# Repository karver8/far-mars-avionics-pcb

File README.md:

# far-mars-avionics-controller

The **far-mars-avionics-controller** is a custom built printed circuit board that performs data aquisition, logging, and communication, all in one highly power effecient, light weight, and compact design. This circuit was built around the FAR/MARS rocket competition, which challenges teams to design a LOX/Methane rocket to accuratley target an altitude of 45,000 feet.

### Features
* Dual(5V/3.3V) Supply ARM Cortex M0+ microcontroller
* 9 multi-purpose 5V I/O pins (+1 DIO PIN)
* Up to 9 12bit and 2 16bit Analog to Digital channels.
* RS-485 Transceiver for long distance LVDS ground communications
* CANbus Transceiver for future feature expansion(untested)
* BNO055 Inertial Measurement Unit
* Locking microSD card slot for secure, vibration resistant data logging
* 5-17V Input Range allowing for versatile power supply.
* Power Effecient enabling the use of a tiny battery
* Very light, weighs less than an ounce!
* Built-in battery charge monitoring.
* Highly accurate crystal for detailed timestamping.

### Firmware

The FAR/MARS rocket uses a FreeRTOS implementation to safley and predictabley manage the various avionics tasks required to launch the rocket. Documentation and development of the firmware for this board can be found in our [far-mars-onboard-firmware](https://github.com/SDSURocketProject/far-mars-onboard-firmware) repository. 

### Documentation
Here is everything you need to interface with this PCB and/or to write your own drivers and firmware:
* [Pinout](/documentation/pinout.pdf "Pinout")
* [Schematic](/documentation/schematic.pdf "Schematic")
* [Mechanical Drawing](/documentation/mech_drawing.pdf "Drawing")
* [Device Datasheet Collection](/documentation/Datasheets "Device Datasheet Collection")

### Assembly
It is highly recommend that you outsource the assembly of this PCB. This design has a lot of tiny surface mount components, on both sides of the board, so unless you have experience reflowing on two sides, this will be almost impossible to assemble yourself. We used MacroFab for the most recent version of this PCB. The current BOM is also optimized to take advantage of their 10-day turnaround service. Here is everything you need to assemble your own avionics controller:
* [Assembly Guide](/assembly#assembly-guide "Instructions")
* [Bill of Materials](/assembly/BOM#bill-of-materials "Bill of Materials")
* [Gerber Files](/assembly/Gerbers)
* [Design Slides](/assembly/Physical%20Summary.pdf "Physical Summary")
* **Schematic & Layout Files are in the top directory**

### Remarks
The far-mars-avionics-controller is entirley functional and usable on any system with similar requirements to the FAR/MARS Lady Elizabeth rocket. Furthermore the CANbus port included in the design, once tested, will also allow for the PCB to interface with virtually any existing CANbus compatible product/system(e.g. Motor Controllers, Thermocouple modules). 

That all said the main purpose of this project was to demonstrate SDSU Rocket Projects ability to design highly purpose built custom electronics, and it was specifically designed around the rules specified by the FAR/MARS rocket competition. This PCB is far from being an all in one solution to any Avionics requirments you may have. The design may find most of its value as a supplement to a larger system.

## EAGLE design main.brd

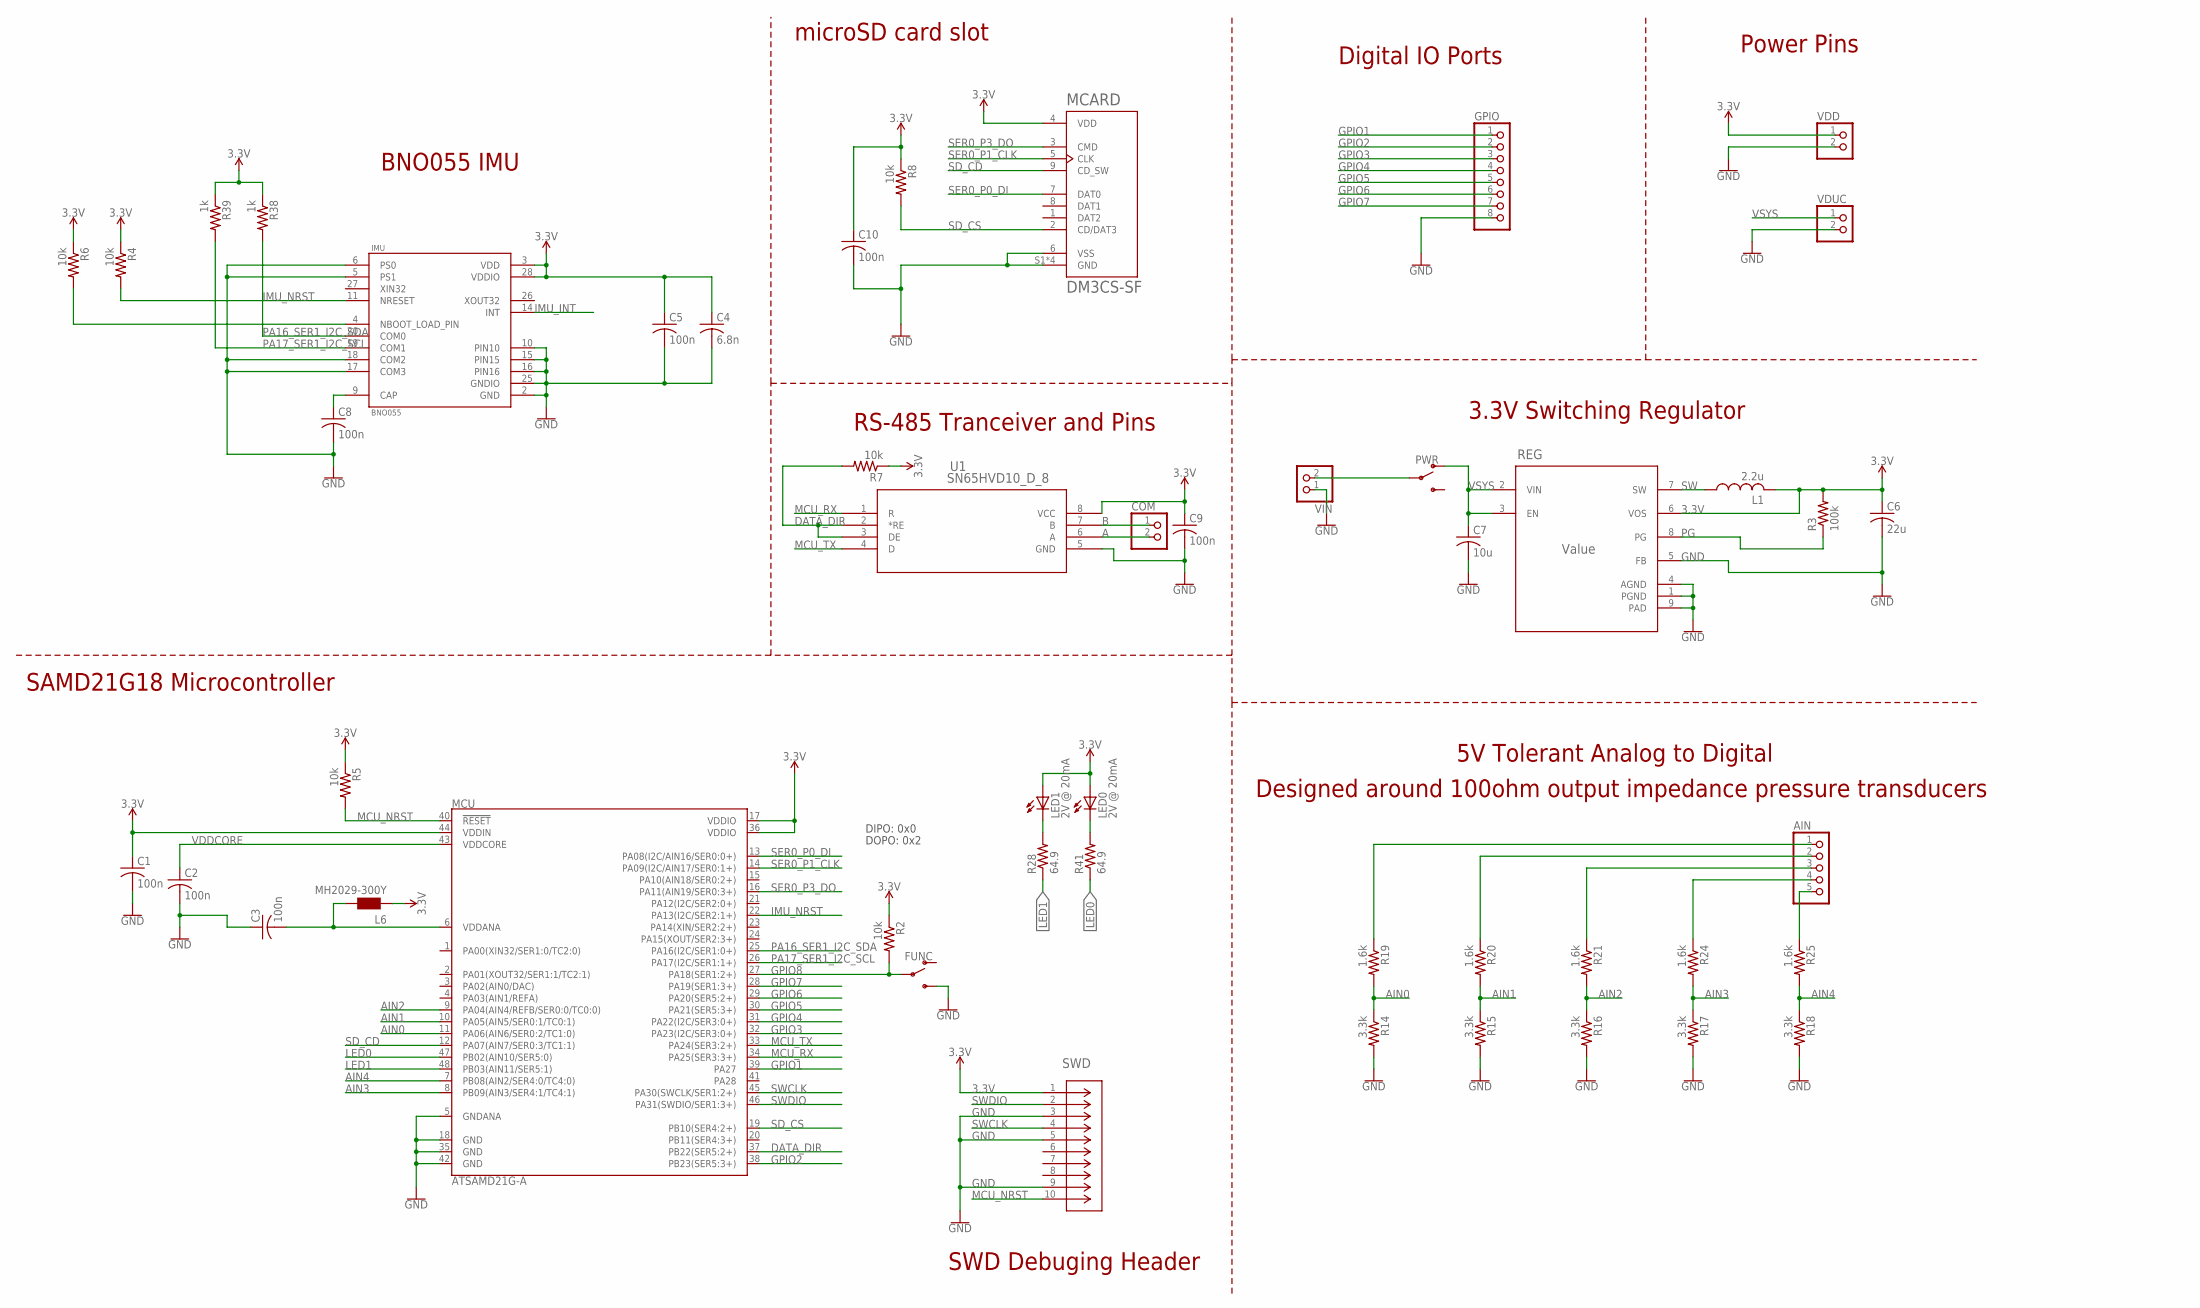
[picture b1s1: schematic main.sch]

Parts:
AIN: PINHD-1X5; 1X05
C1, C2, C3, C5, C8, C9, C10: 100n; C0603
C4: 6.8n; C0603
C6: 22u; C0603
C7: 10u; C0603
COM: PINHD-1X2; 1X02
FUNC: SWITCH-SPDT-SMD-AYZ0202; SWITCH_DPDT_SMD_AYZ0202
GPIO: PINHD-1X8; 1X08
IMU: BNO055; LGA28R50P4X10_380X520X100
L1: 2.2u; L2012C
L6: MH2029-300Y; 0805
LED0, LED1: 2V @ 20mA; CHIPLED_0603
MCARD: DM3CS-SF; HRS_DM3CS-SF
MCU: ATSAMD21G-A; TQFP-48
PWR: SWITCH-SPDT-PTH-11.6X4.0MM; SWITCH_SPDT_PTH_11.6X4.0MM
R2, R4, R5, R6, R7, R8: 10k; R0603
R3: 100k; R0603
R14, R15, R16, R17, R18: 3.3k; R0603
R19, R20, R21, R24, R25: 1.6k; R0603
R28, R41: 64.9; R0603
R38, R39: 1k; R0603
REG: Value; DSG0008A
SWD: DEBUG-HEADER; CONN_MINITEK_2X5_HDR
U1: SN65HVD10_D_8; D8
VDD: PINHD-1X2; 1X02
VDUC: PINHD-1X2; 1X02
VIN: PINHD-1X2; 1X02

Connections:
3.3V: C1.1, C4.1, C5.1, C6.1, C9.1, C10.1, IMU.3 (VDD), IMU.28 (VDDIO), L1.2, L6.1, LED0.A, LED1.A, MCARD.4 (VDD), MCU.17 (VDDIO), MCU.36 (VDDIO), MCU.44 (VDDIN), R2.1, R3.2, R4.1, R5.1, R6.1, R7.1, R8.1, R38.1, R39.1, REG.6 (VOS), SWD.1, U1.8 (VCC), VDD.1
A: COM.2, U1.6 (A)
AIN0: MCU.11 (PA06(AIN6/SER0:2/TC1:0)), R14.1, R19.2
AIN1: MCU.10 (PA05(AIN5/SER0:1/TC0:1)), R15.1, R20.2
AIN2: MCU.9 (PA04(AIN4/REFB/SER0:0/TC0:0)), R16.1, R21.2
AIN3: MCU.8 (PB09(AIN3/SER4:1/TC4:1)), R17.1, R24.2
AIN4: MCU.7 (PB08(AIN2/SER4:0/TC4:0)), R18.1, R25.2
B: COM.1, U1.7 (B)
DATA_DIR: MCU.37 (PB22(SER5:2+)), R7.2, U1.2 (*RE), U1.3 (DE)
GND: C1.2, C2.2, C3.1, C4.2, C5.2, C6.2, C7.2, C8.2, C9.2, C10.2, FUNC.3 (S), GPIO.8, IMU.2 (GND), IMU.5 (PS1), IMU.6 (PS0), IMU.10 (PIN10), IMU.15 (PIN15), IMU.16 (PIN16), IMU.17 (COM3), IMU.18 (COM2), IMU.25 (GNDIO), MCARD.6 (VSS), MCARD.S1 (GND), MCARD.S2 (GND), MCARD.S3 (GND), MCARD.S5 (GND), MCU.5 (GNDANA), MCU.18 (GND), MCU.35 (GND), MCU.42 (GND), R14.2, R15.2, R16.2, R17.2, R18.2, REG.1 (PGND), REG.4 (AGND), REG.5 (FB), REG.9 (PAD), SWD.3, SWD.5, SWD.9, U1.5 (GND), VDD.2, VDUC.2, VIN.1
GPIO1: GPIO.1, MCU.39 (PA27)
GPIO2: GPIO.2, MCU.38 (PB23(SER5:3+))
GPIO3: GPIO.3, MCU.32 (PA23(I2C/SER3:0+))
GPIO4: GPIO.4, MCU.31 (PA22(I2C/SER3:0+))
GPIO5: GPIO.5, MCU.30 (PA21(SER5:3+))
GPIO6: GPIO.6, MCU.29 (PA20(SER5:2+))
GPIO7: GPIO.7, MCU.28 (PA19(SER1:3+))
GPIO8: FUNC.2, MCU.27 (PA18(SER1:2+)), R2.2
IMU_INT: IMU.14 (INT)
IMU_NRST: IMU.11 (NRESET), MCU.22 (PA13(I2C/SER2:1+)), R4.2
LED0: MCU.47 (PB02(AIN10/SER5:0)), R41.1
LED1: MCU.48 (PB03(AIN11/SER5:1)), R28.1
MCU_NRST: MCU.40 (!RESET!), R5.2, SWD.10
MCU_RX: MCU.34 (PA25(SER3:3+)), U1.1 (R)
MCU_TX: MCU.33 (PA24(SER3:2+)), U1.4 (D)
unnamed: AIN.2, R20.1
unnamed: C3.2, L6.2, MCU.6 (VDDANA)
unnamed: AIN.3, R21.1
unnamed: AIN.4, R24.1
unnamed: AIN.5, R25.1
unnamed: LED0.C, R41.2
unnamed: AIN.1, R19.1
unnamed: PWR.2, VIN.2
unnamed: C8.1, IMU.9 (CAP)
unnamed: IMU.4 (NBOOT_LOAD_PIN), R6.2
unnamed: LED1.C, R28.2
PA16_SER1_I2C_SDA: IMU.20 (COM0), MCU.25 (PA16(I2C/SER1:0+)), R38.2
PA17_SER1_I2C_SCL: IMU.19 (COM1), MCU.26 (PA17(I2C/SER1:1+)), R39.2
PG: R3.1, REG.8 (PG)
SD_CD: MCARD.9 (CD_SW), MCU.12 (PA07(AIN7/SER0:3/TC1:1))
SD_CS: MCARD.2 (CD/DAT3), MCU.19 (PB10(SER4:2+)), R8.2
SER0_P0_DI: MCARD.7 (DAT0), MCU.13 (PA08(I2C/AIN16/SER0:0+))
SER0_P1_CLK: MCARD.5 (CLK), MCU.14 (PA09(I2C/AIN17/SER0:1+))
SER0_P3_DO: MCARD.3 (CMD), MCU.16 (PA11(AIN19/SER0:3+))
SW: L1.1, REG.7 (SW)
SWCLK: MCU.45 (PA30(SWCLK/SER1:2+)), SWD.4
SWDIO: MCU.46 (PA31(SWDIO/SER1:3+)), SWD.2
VDDCORE: C2.1, MCU.43 (VDDCORE)
VSYS: C7.1, PWR.1 (O), REG.2 (VIN), REG.3 (EN), VDUC.1

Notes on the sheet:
DIPO: 0x0
DOPO: 0x2
RS-485 Tranceiver and Pins
5V Tolerant Analog to Digital
Designed around 100ohm output impedance pressure transducers
SAMD21G18 Microcontroller
SWD Debuging Header
BNO055 IMU
microSD card slot
Digital IO Ports
Power Pins
3.3V Switching Regulator

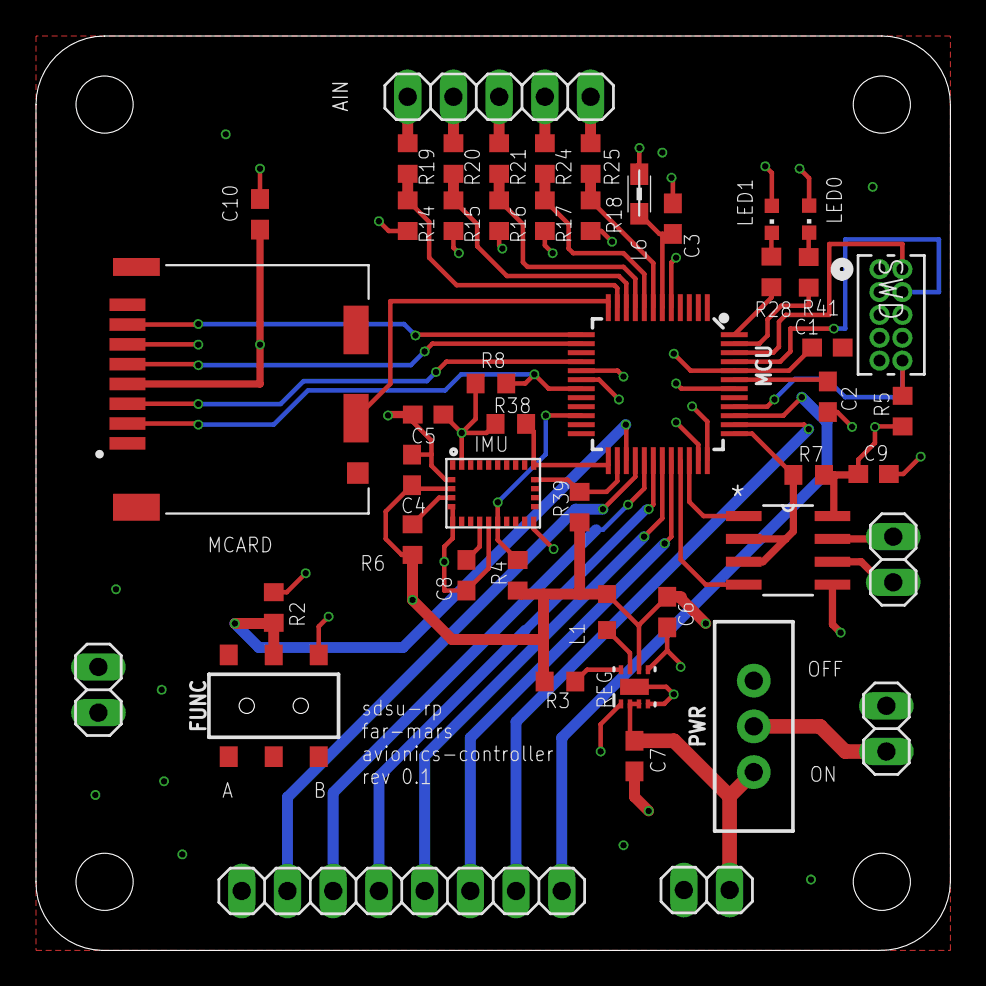
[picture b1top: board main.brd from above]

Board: 4 copper layers, 50.8 x 50.8 mm, 54 parts (1 on the bottom side), 48 nets.

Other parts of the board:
U$1, U$2, U$3, U$4: DRILL_0.1250
U$5: RP-LOGO-DPIFIX

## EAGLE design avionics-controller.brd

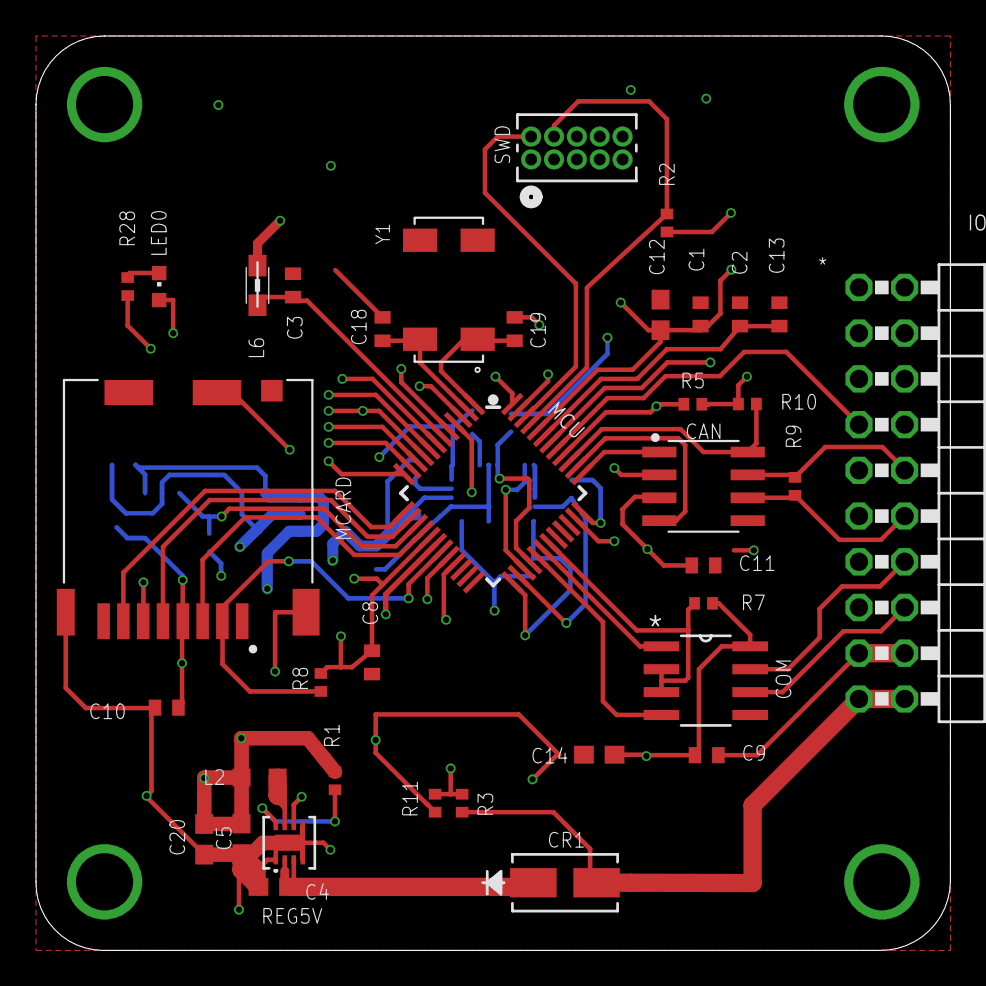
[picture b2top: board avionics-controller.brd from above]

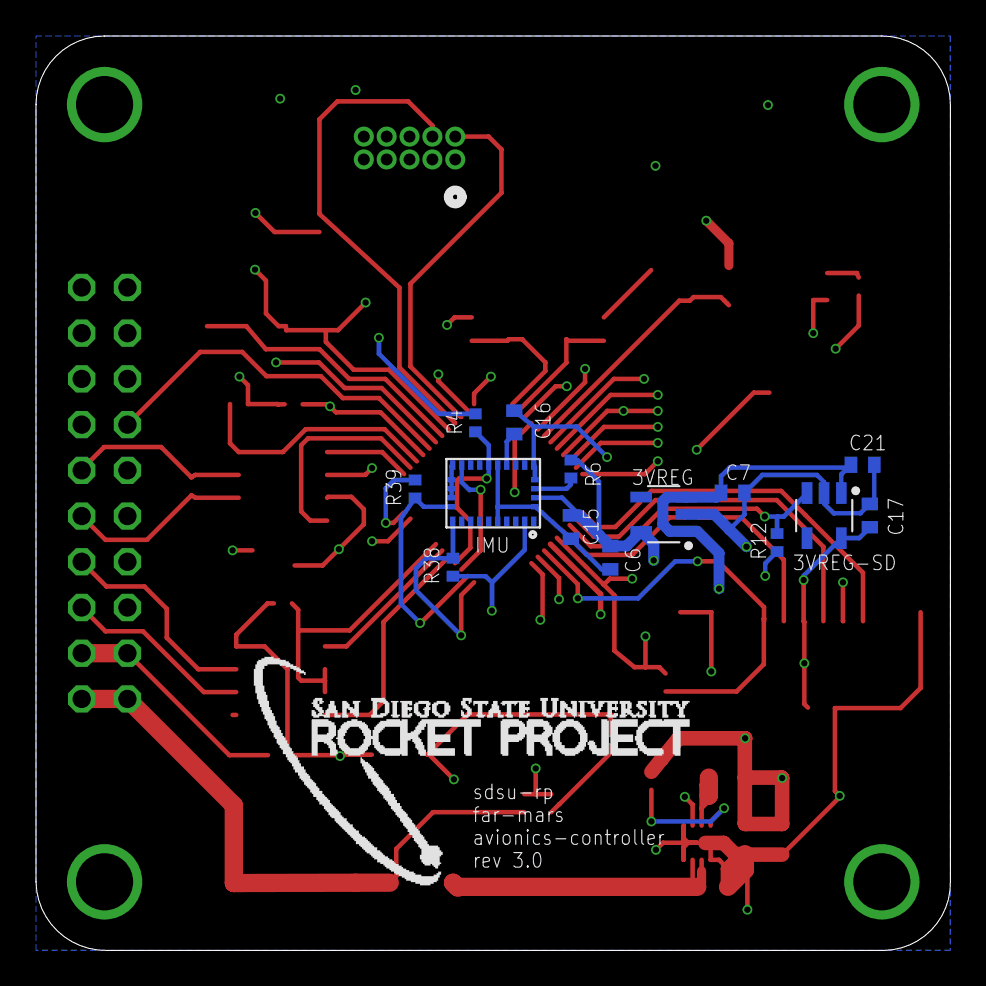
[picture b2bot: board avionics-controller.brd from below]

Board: 4 copper layers, 50.8 x 50.8 mm, 52 parts (15 on the bottom side), 51 nets.

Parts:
3VREG, 3VREG-SD: 3.3VREGULATOR; SOT95P280X110-5
C1, C2, C3, C8, C9, C10, C11, C15, C16: 100n; C0402
C4, C5, C12, C14, C20: 10u; C0603
C6, C7, C13, C17, C21: 1u; C0402
C18, C19: 15p; C0402
CAN: MCP2561T-E8SOIC; SOIC127P600X175-8
CR1: B160-13-FSMA-M; SMA-M
IMU: BNO055; LGA28R50P4X10_380X520X100
IO: 2X10/90
L2: 2.2u; L2012C
L6: MH2029-300Y; 0805
LED0: 2V @ 20mA; CHIPLED_0603
MCARD: DM3CS-SF; HRS_DM3CS-SF
MCU: ATSAMC21G18-A; TQFP-48
R1: 100k; R0402
R2, R11, R38, R39: 1k; R0402
R3, R4, R5, R6, R7, R8, R10, R12: 10k; R0402
R9, R28: 120; R0402
REG5V: TPS62163DSGT; DSG8_1P6X0P9
SWD: DEBUG-HEADER; CONN_MINITEK_2X5_HDR
U1: SN65HVD10_D_8; D8
U$6: RP-LOGO
Y1: ABS25-32.768KHZ; ABS25-32.768KHZ-6-T

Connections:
3.3V: 3VREG.5, C6.1, C8.1, C9.1, C14.1, C15.1, IMU.3, IMU.28, LED0.A, MCU.17, MCU.36, R4.1, R6.1, R7.1, R8.1, R38.1, R39.1, U1.8
3V_SD: 3VREG-SD.5, C10.1, C17.1, MCARD.4
5V: 3VREG.1, 3VREG.3, 3VREG-SD.1, C1.1, C5.1, C7.1, C11.1, C12.1, C20.1, C21.1, CAN.3, IO.1, L2.2, L6.1, MCU.44, R1.2, R2.1, R5.1, R10.1, R12.1, REG5V.6, SWD.1
A: IO.16, U1.6
B: IO.14, U1.7
CANH: CAN.7, IO.10, R9.2
CANL: CAN.6, IO.12, R9.1
CAN_RX_5V: CAN.4, MCU.38
CAN_STBY_5V: CAN.8, MCU.39, R10.2
CAN_TX_5V: CAN.1, MCU.37
DATA_DIR: MCU.31, R7.2, U1.2, U1.3
GND: 3VREG.2, 3VREG-SD.2, C1.2, C2.2, C3.1, C4.2, C5.2, C6.2, C7.2, C8.2, C9.2, C10.2, C11.2, C12.2, C13.2, C14.2, C15.2, C16.2, C17.2, C18.2, C19.2, C20.2, C21.2, CAN.2, IMU.2, IMU.5, IMU.6, IMU.10, IMU.15, IMU.16, IMU.17, IMU.18, IMU.25, IO.2, IO.17, IO.18, MCARD.6, MCARD.S1, MCARD.S2, MCARD.S3, MCARD.S5, MCU.5, MCU.18, MCU.35, MCU.42, R11.1, REG5V.1, SWD.3, SWD.5, SWD.9, U1.5
IMU_INT: IMU.14, MCU.27
IMU_NRST: IMU.11, MCU.28, R4.2
LED0: MCU.21, R28.1
MCU_NRST: MCU.40, R5.2, SWD.10
MCU_RX_3.3V: MCU.30, U1.1
MCU_TX_3.3V: MCU.29, U1.4
unnamed: R1.1, REG5V.8
unnamed: C3.2, L6.2, MCU.6
unnamed: L2.1, REG5V.7
unnamed: REG5V.4, REG5V.5, REG5V.9
unnamed: C4.1, CR1.1, REG5V.2, REG5V.3
unnamed: C19.1, MCU.1, Y1.1
unnamed: C18.1, MCU.2, Y1.4
unnamed: C16.1, IMU.9
unnamed: IMU.4, R6.2
unnamed: LED0.C, R28.2
PA02/AIN0: IO.5, MCU.3
PA04/AIN4: IO.9, MCU.9
PA05/AIN5: IO.11, MCU.10
PA06/AIN6: IO.13, MCU.11
PA07/AIN7: IO.15, MCU.12
PA16_SER1_I2C_SDA: IMU.20, MCU.25, R38.2
PA17_SER1_I2C_SCL: IMU.19, MCU.26, R39.2
PA28: IO.7, MCU.41
PB02/AIN10: IO.3, MCU.47
PB03/AIN11: IO.4, MCU.48
PB08/AIN2: IO.6, MCU.7
PB09/AIN3: IO.8, MCU.8
SD_CD: MCARD.9, MCU.20
SD_CS: MCARD.2, MCU.19, R8.2
SD_EN: 3VREG-SD.3, MCU.15, R12.2
SER0_P0_DI: MCARD.7, MCU.13
SER0_P1_CLK: MCARD.5, MCU.14
SER0_P3_DO: MCARD.3, MCU.16
SWCLK: MCU.45, R2.2, SWD.4
SWDIO: MCU.46, SWD.2
VBAT_SENSE: MCU.4, R3.1, R11.2
VDDCORE: C2.1, C13.1, MCU.43
V_BATT: CR1.2, IO.19, IO.20, R3.2

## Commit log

2018-02-09 Copied over from far-mars-onboard-pcb
2018-02-09 First Layout and Schematic
2018-02-09 Added some wires
2018-02-09 Added gnd pour
2018-02-11 Added IMU
2018-02-17 Schematic and Layout Optimizations
    Reconfigured a couple serial pins to make trace routing easier. Placed all compnents, just need to route and label.
2018-02-17 Routed everything
2018-02-17 Small tweaks before labels
2018-02-17 Labeled compenents added logos
2018-02-18 Some logo dpi fixes
    OSHpark wouldn't except a silkscreen above 400 dpi
2018-02-18 Added board renderings for readme
2018-02-18 Render resize
2018-02-18 More readme stuff
2018-02-18 Added high res renders
2018-02-18 Updated bom
2018-02-18 Added links to BOM
2018-02-18 Small switch adjustment, and render update for this change
2018-02-19 Added headers and housings table to readme
2018-02-19 Added misc table to readme
2018-02-19 Organized Schematic
    Added borders, boxes, and labels
2018-02-19 Added schematic image capture
2018-02-20 Layout overview
2018-02-20 Fixed poly fill not connecting to all pins
2018-02-23 Changed coms transceiver, and updated documentation
    Also updated bill of materials
2018-04-15 Switched out SWD header for one with bigger drills
2018-06-09 Added some traces, added a reset signal to IMU
2018-06-10 Added Higned SD, rearranged silk
    Added new hinged MicroSD for stability purposes, this sd card will be operating in a high g, high vibration enviornment and a spring ejection slot is not adequate. I also rearranged the labels on the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
2018-06-12 Updated some supporting documents
2018-06-12 Update microSD in bom to match new footprint in eagle files
2019-01-31 intial rev 3.0 update
    Initial files and structure of core documentation for rev 3.0 of the far-mars avionics computer. Will be updating and adding documents soon.
2019-02-01 Added Documentation and BOM
    Added some IC datasheets and updated a few readmes to display bom and added CSV for bom
2019-02-01 Update README.md
    Added links
2019-02-06 Updated documentation(pinout, bom) and made small layout adjustment
    Added another BOM, updated BOM readme to remove markdown table and replaced with links, fixed small layout error that caused sd card to short GND to filters 5V pad when fully open. Added more datashe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
2019-02-06 Added Gerbers and Datasheet Index
2019-02-06 Minor edits on readmes, Added Assembly Guide
2019-02-06 Update README.md
    Fixed assembly guide formatting
2019-02-08 Added updated Pinout, Mechanical Drawing, and Electrical Schematic PDFs
2019-02-08 Update README.md
    Fixed schematic pdf link in main readme
2019-04-04 add empty altium project
2019-04-05 Initial include of altium translation of OBC rev3
2019-04-05 update gitignore
2019-04-05 move altium files to new directory
2019-04-27 Added rest of the datasheets, made some small documentation changes for clarity.
2019-04-27 Added easy navigation links for datasheets
2020-08-07 Update README.md
    Fixed image URL.
2020-08-07 Updated even more URLs as they all broke when I forked this repository.

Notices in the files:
parts and their libraries:
SparkFun-IC-Microcontroller: Licensing: Creative Commons ShareAlike 4.0 International - https://creativecommons.org/licenses/by-sa/4.0
